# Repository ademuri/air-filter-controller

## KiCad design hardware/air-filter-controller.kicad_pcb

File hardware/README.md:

## Design decisions

### Power supply scheme

The ESP32-S3 uses 3.3V. I want onboard indicator LEDs, and the option to have offboard LEDs as well. Using addressable WS2812-type LEDs is flexible. These need a 5V supply. The fans draw 12V, so this necessitates two voltage regulators.

One option would be to use separate buck converters for both the 5V and 3.3V rails.

With no offboard LEDs, the 5V rail power draw will be low. WS2812B LEDs consume roughly 1mA each when idle. When lit at a fully-saturated color, they will consume about 20mA each. There are four onboard LEDs, so this means 4mA idle, and 80mA when lit.

This is relatively low power consumption. However, offboard LEDs may need significantly more power. If, for example, a 16-LED ring is used, then up to 400mA total may be needed.

During normal operation, the indicator light will be off. So, most of the time, the 5V current draw will be low.

To convert from the 12V supply to 5V, we'll use a buck converter. If we size the inductor for the maximum current draw, then the converter will potentially be noisy during typical operation.

So, we should instead use a linear regulator to convert the 5V to 3.3V, if possible. This will simplify the design, and increase the minimum current draw on the buck converter. Is it feasible?

The ESP32-S3 datasheet says that the power supply should support at least 500mA. The AMS1117-3.3 supports 1A max. The typical power draw of the ESP32-S3 running our ESPHome configuration is 30-120mA. A linear regulator burns the excess voltage as heat. For (worst-case) typical operation, the power consumed by the regulator will be `.12A * (5V - 3.3V) = 200mW`. This is acceptable.

Using [this buck converter calculator](http://schmidt-walter-schaltnetzteile.de/smps_e/abw_smps_e.html), a 100uH inductor means that the maximum ripple current will be about 50mA.

The chosen inductor (`SWPA8065S101MT`) has a max DC resistance of 0.28Ω, and a max heat-rating current of 1.35A. If the ESP32-S3 draws 500mA, this leaves >500mA for LEDs. This is sufficient.

#### Filtering

I did a conducted emissions pre-test for v1.0, using a dual 5uH LISN between the board and an adjustable DC power supply. With the board on and idle (30-40mA pulled from the 12V source), I saw a few concerning peaks:

- A sharp peak around 725 kHz, about 10dB above the limit
- Sharp peaks around 3.6kHz, 1.4 MHz, 2.2 MHz, and 3.6 MHz - these are >3dB below the limit
- Broadband noise between 300kHz to 400kHz

Increasing the load on the buck converter slightly by turning on the indicator LED to full white (50-55mA pulled @12V), the peaks get sharper, with the 365 kHz peak exceeding the limit by 6dB, and the 1.4MHz peak exceeding the limit by ~8dB.

There isn't much change with one fan plugged in on full power.

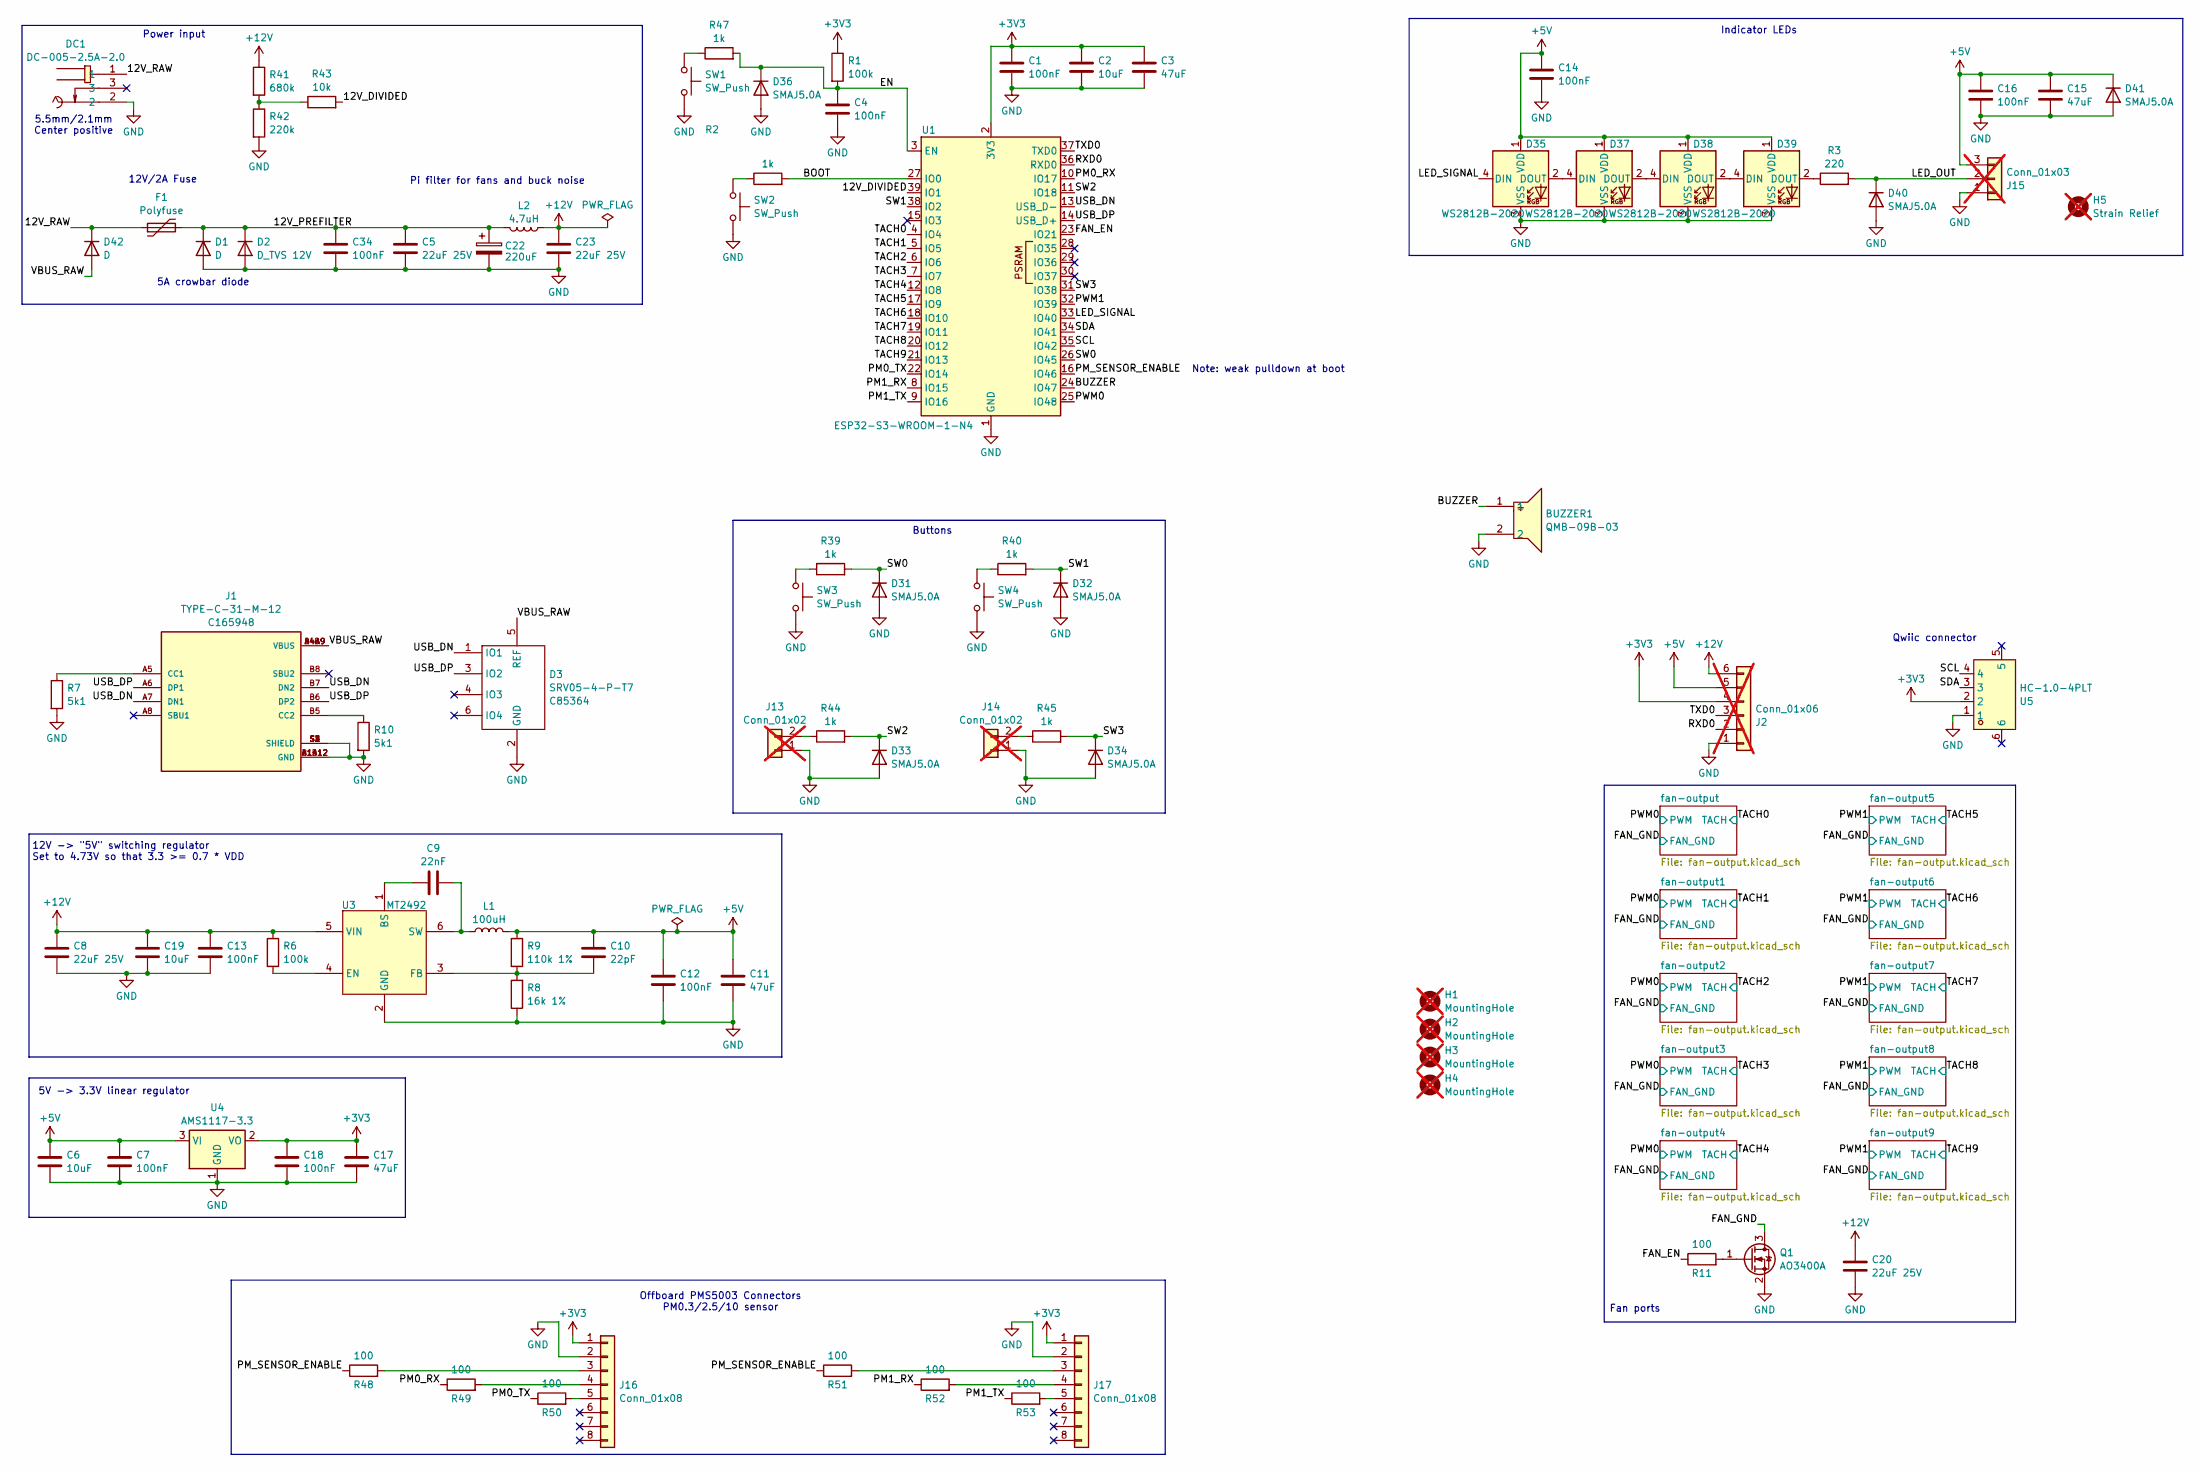
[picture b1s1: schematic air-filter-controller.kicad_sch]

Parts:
BUZZER1: QMB-09B-03; BUZ-TH_BD9.0-P4.00-D0.6-FD; LCSC C96256
C1, C4, C7, C12, C13, C14, C16, C18, C34: 100nF; C_0402_1005Metric; LCSC C307331
C2, C6, C19: 10uF; C_0603_1608Metric; LCSC C96446
C3, C11, C15, C17: 47uF; C_1206_3216Metric; LCSC C96123
C5, C8, C20, C23: 22uF 25V; C_1206_3216Metric; LCSC C12891
C9: 22nF; C_0402_1005Metric; LCSC C1532
C10: 22pF; C_0402_1005Metric; LCSC C1555
C22: 220uF; CP_Elec_8x10; LCSC C134765
D1, D42: D; D_SMA; MPN SS54; LCSC C22452
D2: D_TVS 12V; D_SMA; MPN SMAJ12A-E3/61; LCSC C89613
D3: SRV05-4-P-T7; SOT-23-6; LCSC C85364
D31, D32, D33, D34, D36, D40, D41: SMAJ5.0A; D_SMA; MPN SMAJ5.0A; LCSC C113952
D35, D37, D38, D39: WS2812B-2020; LED-SMD_4P-L2.0-W2.0-TL_WS2812B-2020; LCSC C965555
DC1: DC-005-2.5A-2.0; CONN-TH_DC-005-2.5A-2.0; LCSC C319099
F1: Polyfuse; Fuse_1812_4532Metric; MPN 1812L200/12DR; LCSC C315901
H1, H2, H3, H4: MountingHole; MountingHole_3.2mm_M3_ISO7380; not fitted
H5: Strain Relief; 3_pin_2.54mm_pitch_strain_relief; not fitted
J1: TYPE-C-31-M-12; HRO_TYPE-C-31-M-12; PARTREV A; LCSC C165948
J2: Conn_01x06; PinHeader_1x06_P2.54mm_Vertical; not fitted
J13, J14: Conn_01x02; PinHeader_1x02_P2.54mm_Vertical; not fitted
J15: Conn_01x03; PinHeader_1x03_P2.54mm_Vertical; not fitted
J16, J17: Conn_01x08; CONN-TH_8P-P1.25_HCTL_HC-1.25-8A; LCSC C2845526
L1: 100uH; L_Sunlord_SWPA8040S; MPN SWPA8065S101MT; LCSC C334254
L2: 4.7uH; L_Sunlord_SWPA4030S; MPN SWPA4030S4R7MT; LCSC C57269
Q1: AO3400A; SOT-23; LCSC C20917
R1, R6: 100k; R_0402_1005Metric; LCSC C25741
R2, R39, R40, R44, R45, R47: 1k; R_0402_1005Metric; LCSC C11702
R3: 220; R_0603_1608Metric_Pad0.98x0.95mm_HandSolder; LCSC C22962
R7, R10: 5k1; R_0402_1005Metric; LCSC C25905
R8: 16k 1%; R_0402_1005Metric; LCSC C25759
R9: 110k 1%; R_0402_1005Metric; LCSC C25745
R11: 100; R_0402_1005Metric; LCSC C25076
R41: 680k; R_0402_1005Metric; LCSC C4131
R42: 220k; R_0402_1005Metric; LCSC C25767
R43: 10k; R_0402_1005Metric; LCSC C25744
R48, R49, R50, R51, R52, R53: 100; R_0603_1608Metric_Pad0.98x0.95mm_HandSolder; LCSC C22775
SW1, SW2, SW3, SW4: SW_Push; SW_TACTILE_5.1MM_TS-1187A-C-D-B; LCSC C318884
U1: ESP32-S3-WROOM-1-N4; ESP32-S3-WROOM-1; LCSC C2913197
U3: MT2492; SOT-23-6_L2.9-W1.6-P0.95-LS2.8-BL; LCSC C89358
U4: AMS1117-3.3; SOT-223-3_TabPin2; LCSC C6186
U5: HC-1.0-4PLT; CONN-SMD_4P-P1.00_HC-1.0-4PLT; LCSC C2845372

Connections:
+3V3: C1.1, C2.1, C3.1, C17.1, C18.1, J2.4, J16.1, J17.1, R1.1, U1.2 (3V3), U4.2 (VO), U5.2; also elsewhere on the board
+5V: C6.1, C7.1, C10.2, C11.1, C12.1, C14.1, C15.1, C16.1, D35.1 (VDD), D37.1 (VDD), D38.1 (VDD), D39.1 (VDD), D41.1 (K), J2.5, J15.3, L1.2, R9.1, U4.3 (VI)
+12V: C8.1, C13.1, C19.1, C20.1, C23.1, J2.6, L2.1, R6.1, R41.1, U3.5 (VIN); also elsewhere on the board
/12V_DIVIDED: R43.2, U1.39 (IO1)
/12V_PREFILTER: C5.1, C22.1, C34.1, D1.1 (K), D2.1 (K), F1.2, L2.2
/12V_RAW: D42.1 (K), DC1.1, F1.1
/BOOT: R2.2, U1.27 (IO0)
/BUZZER: BUZZER1.1, U1.24 (IO47)
/EN: C4.1, D36.1 (K), R1.2, R47.2, U1.3 (EN)
/FAN_EN: R11.1, U1.23 (IO21)
/FAN_GND: Q1.3 (D); also elsewhere on the board
/LED_OUT: D40.1 (K), J15.2, R3.2
/LED_SIGNAL: D35.4 (DIN), U1.33 (IO40)
/PM0_RX: R49.1, U1.10 (IO17)
/PM0_TX: R50.1, U1.22 (IO14)
/PM1_RX: R52.1, U1.8 (IO15)
/PM1_TX: R53.1, U1.9 (IO16)
/PM_SENSOR_ENABLE: R48.1, R51.1, U1.16 (IO46)
/PWM0: U1.25 (IO48); also elsewhere on the board
/PWM1: U1.32 (IO39); also elsewhere on the board
/RXD0: J2.2, U1.36 (RXD0)
/SCL: U1.35 (IO42), U5.4
/SDA: U1.34 (IO41), U5.3
/SW0: D31.1 (K), R39.2, U1.26 (IO45)
/SW1: D32.1 (K), R40.2, U1.38 (IO2)
/SW2: D33.1 (K), R44.2, U1.11 (IO18)
/SW3: D34.1 (K), R45.2, U1.31 (IO38)
/TACH0: U1.4 (IO4); also elsewhere on the board
/TACH1: U1.5 (IO5); also elsewhere on the board
/TACH2: U1.6 (IO6); also elsewhere on the board
/TACH3: U1.7 (IO7); also elsewhere on the board
/TACH4: U1.12 (IO8); also elsewhere on the board
/TACH5: U1.17 (IO9); also elsewhere on the board
/TACH6: U1.18 (IO10); also elsewhere on the board
/TACH7: U1.19 (IO11); also elsewhere on the board
/TACH8: U1.20 (IO12); also elsewhere on the board
/TACH9: U1.21 (IO13); also elsewhere on the board
/TXD0: J2.3, U1.37 (TXD0)
/USB_DN: D3.1 (IO1), J1.A7 (DN1), J1.B7 (DN2), U1.13 (USB_D-)
/USB_DP: D3.3 (IO2), J1.A6 (DP1), J1.B6 (DP2), U1.14 (USB_D+)
/VBUS_RAW: D3.5 (REF), D42.2 (A), J1.A4B9 (VBUS), J1.B4A9 (VBUS)
GND: BUZZER1.2, C1.2, C2.2, C3.2, C4.2, C5.2, C6.2, C7.2, C8.2, C11.2, C12.2, C13.2, C14.2, C15.2, C16.2, C17.2, C18.2, C19.2, C20.2, C22.2, C23.2, C34.2, D1.2 (A), D2.2 (A), D3.2 (GND), D31.2 (A), D32.2 (A), D33.2 (A), D34.2 (A), D35.3 (VSS), D36.2 (A), D37.3 (VSS), D38.3 (VSS), D39.3 (VSS), D40.2 (A), D41.2 (A), DC1.2, J1.A1B12 (GND), J1.B1A12 (GND), J1.S1 (SHIELD), J1.S2 (SHIELD), J1.S3 (SHIELD), J1.S4 (SHIELD), J2.1, J13.1, J14.1, J15.1, J16.2, J17.2, Q1.2 (S), R7.2, R8.1, R10.2, R42.2, SW1.2, SW2.2, SW3.2, SW4.2, U1.1 (GND), U1.40 (GND), U1.41 (GND), U3.2 (GND), U4.1 (GND), U5.1; also elsewhere on the board
unnamed: D35.2 (DOUT), D37.4 (DIN)
unnamed: D37.2 (DOUT), D38.4 (DIN)
unnamed: D38.2 (DOUT), D39.4 (DIN)
unnamed: D39.2 (DOUT), R3.1
unnamed: J1.A5 (CC1), R7.1
unnamed: J1.B5 (CC2), R10.1
unnamed: J13.2, R44.1
unnamed: J14.2, R45.1
unnamed: J16.3, R48.2
unnamed: J16.4, R49.2
unnamed: J16.5, R50.2
unnamed: J17.3, R51.2
unnamed: J17.4, R52.2
unnamed: J17.5, R53.2
unnamed: Q1.1 (G), R11.2
unnamed: R2.1, SW2.1
unnamed: R39.1, SW3.1
unnamed: R40.1, SW4.1
unnamed: R41.2, R42.1, R43.1
unnamed: R47.1, SW1.1
unnamed: C9.1, U3.1 (BS)
unnamed: R6.2, U3.4 (EN)
unnamed: C10.1, R8.2, R9.2, U3.3 (FB)
unnamed: C9.2, L1.1, U3.6 (SW)

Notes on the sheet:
Power input
Fan ports
Note: weak pulldown at boot
Pi filter for fans and buck noise
5.5mm/2.1mm Center positive
5V -> 3.3V linear regulator
Qwiic connector
12V -> "5V" switching regulator Set to 4.73V so that 3.3 >= 0.7 * VDD
Offboard PMS5003 Connectors PM0.3/2.5/10 sensor
5A crowbar diode
12V/2A Fuse
Indicator LEDs
Buttons

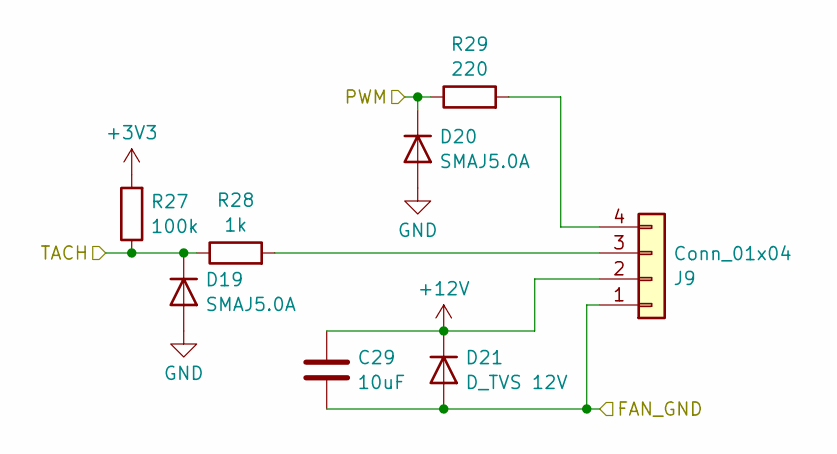
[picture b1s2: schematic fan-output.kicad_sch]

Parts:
C29: 10uF; C_0603_1608Metric; LCSC C96446
D19, D20: SMAJ5.0A; D_SMA; MPN SMAJ5.0A; LCSC C113952
D21: D_TVS 12V; D_SMA; MPN SMAJ12A-E3/61; LCSC C89613
J9: Conn_01x04; CONN-TH_47053-1000; MPN 470531000; LCSC C240840
R27: 100k; R_0603_1608Metric_Pad0.98x0.95mm_HandSolder; LCSC C25803
R28: 1k; R_0402_1005Metric; LCSC C11702
R29: 220; R_0603_1608Metric_Pad0.98x0.95mm_HandSolder; LCSC C22962

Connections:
+3V3: R27.2; also elsewhere on the board
+12V: C29.1, D21.1 (K), J9.2; also elsewhere on the board
/FAN_GND: C29.2, D21.2 (A), J9.1; also elsewhere on the board
/PWM1: D20.1 (K), R29.1; also elsewhere on the board
/TACH5: D19.1 (K), R27.1, R28.1; also elsewhere on the board
GND: D19.2 (A), D20.2 (A); also elsewhere on the board
unnamed: J9.3, R28.2
unnamed: J9.4, R29.2

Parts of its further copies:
C24, C25, C26, C27, C28, C30, C31, C32, C33: 10uF; C_0603_1608Metric; LCSC C96446
D4, D9, D12, D15, D18, D24, D27, D30, D45: D_TVS 12V; D_SMA; MPN SMAJ12A-E3/61; LCSC C89613
D5, D6, D7, D8, D10, D11, D13, D14, D16, D17, D22, D23, D25, D26, D28, D29, D43, D44: SMAJ5.0A; D_SMA; MPN SMAJ5.0A; LCSC C113952
J3, J4, J5, J6, J7, J8, J10, J11, J12: Conn_01x04; CONN-TH_47053-1000; MPN 470531000; LCSC C240840
R4, R12, R15, R18, R21, R24, R30, R33, R36: 100k; R_0603_1608Metric_Pad0.98x0.95mm_HandSolder; LCSC C25803
R5, R13, R16, R19, R22, R25, R31, R34, R37: 1k; R_0402_1005Metric; LCSC C11702
R14, R17, R20, R23, R26, R32, R35, R38, R46: 220; R_0603_1608Metric_Pad0.98x0.95mm_HandSolder; LCSC C22962

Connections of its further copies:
+3V3: R4.2, R12.2, R15.2, R18.2, R21.2, R24.2, R30.2, R33.2, R36.2; also elsewhere on the board
+12V: C24.1, C25.1, C26.1, C27.1, C28.1, C30.1, C31.1, C32.1, C33.1, D4.1 (K), D9.1 (K), D12.1 (K), D15.1 (K), D18.1 (K), D24.1 (K), D27.1 (K), D30.1 (K), D45.1 (K), J3.2, J4.2, J5.2, J6.2, J7.2, J8.2, J10.2, J11.2, J12.2; also elsewhere on the board
/FAN_GND: C24.2, C25.2, C26.2, C27.2, C28.2, C30.2, C31.2, C32.2, C33.2, D4.2 (A), D9.2 (A), D12.2 (A), D15.2 (A), D18.2 (A), D24.2 (A), D27.2 (A), D30.2 (A), D45.2 (A), J3.1, J4.1, J5.1, J6.1, J7.1, J8.1, J10.1, J11.1, J12.1; also elsewhere on the board
/PWM0: D6.1 (K), D8.1 (K), D11.1 (K), D14.1 (K), D17.1 (K), R14.1, R17.1, R20.1, R23.1, R26.1; also elsewhere on the board
/PWM1: D23.1 (K), D26.1 (K), D29.1 (K), D44.1 (K), R32.1, R35.1, R38.1, R46.1; also elsewhere on the board
/TACH0: D5.1 (K), R13.1, R15.1; also elsewhere on the board
/TACH1: D7.1 (K), R12.1, R16.1; also elsewhere on the board
/TACH2: D10.1 (K), R18.1, R19.1; also elsewhere on the board
/TACH3: D13.1 (K), R21.1, R22.1; also elsewhere on the board
/TACH4: D16.1 (K), R24.1, R25.1; also elsewhere on the board
/TACH6: D22.1 (K), R30.1, R31.1; also elsewhere on the board
/TACH7: D25.1 (K), R33.1, R34.1; also elsewhere on the board
/TACH8: D28.1 (K), R36.1, R37.1; also elsewhere on the board
/TACH9: D43.1 (K), R4.1, R5.1; also elsewhere on the board
GND: D5.2 (A), D6.2 (A), D7.2 (A), D8.2 (A), D10.2 (A), D11.2 (A), D13.2 (A), D14.2 (A), D16.2 (A), D17.2 (A), D22.2 (A), D23.2 (A), D25.2 (A), D26.2 (A), D28.2 (A), D29.2 (A), D43.2 (A), D44.2 (A); also elsewhere on the board
unnamed: J3.3, R16.2
unnamed: J3.4, R17.2
unnamed: J4.3, R5.2
unnamed: J4.4, R46.2
unnamed: J5.3, R13.2
unnamed: J5.4, R14.2
unnamed: J6.3, R19.2
unnamed: J6.4, R20.2
unnamed: J7.3, R22.2
unnamed: J7.4, R23.2
unnamed: J8.3, R25.2
unnamed: J8.4, R26.2
unnamed: J10.3, R31.2
unnamed: J10.4, R32.2
unnamed: J11.3, R34.2
unnamed: J11.4, R35.2
unnamed: J12.3, R37.2
unnamed: J12.4, R38.2

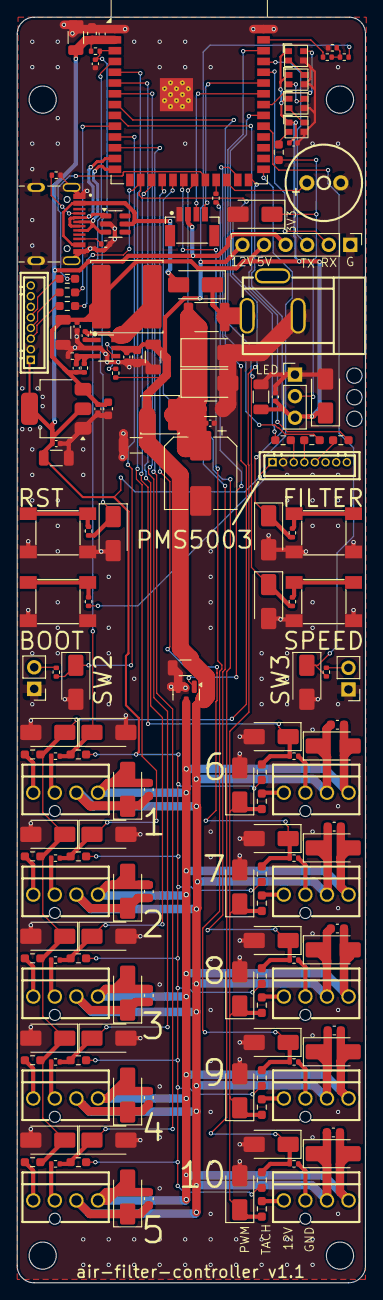
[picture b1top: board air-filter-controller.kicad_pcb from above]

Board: 4 copper layers, 41.0 x 149.0 mm, 167 parts (0 on the bottom side), 86 nets.

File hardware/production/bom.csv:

Designator,Footprint,Quantity,Value,LCSC Part #
BUZZER1,BUZ-TH_BD9.0-P4.00-D0.6-FD,1,QMB-09B-03,
"C1, C12, C13, C14, C16, C18, C34, C4, C7",0402,9,100nF,C307331
C10,0402,1,22pF,C1555
"C11, C15, C17, C3",1206,4,47uF,C96123
"C19, C2, C24, C25, C26, C27, C28, C29, C30, C31, C32, C33, C6",0603,13,10uF,C96446
"C20, C23, C5, C8",1206,4,22uF 25V,C12891
C22,CP_Elec_8x10,1,220uF,C134765
C9,0402,1,22nF,C1532
"D1, D42",D_SMA,2,D,C22452
"D10, D11, D13, D14, D16, D17, D19, D20, D22, D23, D25, D26, D28, D29, D31, D32, D33, D34, D36, D40, D41, D43, D44, D5, D6, D7, D8",D_SMA,27,SMAJ5.0A,C113952
"D12, D15, D18, D2, D21, D24, D27, D30, D4, D45, D9",D_SMA,11,D_TVS 12V,C89613
D3,SOT-23-6,1,SRV05-4-P-T7,C85364
"D35, D37, D38, D39",LED-SMD_4P-L2.0-W2.0-TL_WS2812B-2020,4,WS2812B-2020,C965555
DC1,CONN-TH_DC-005-2.5A-2.0,1,DC-005-2.5A-2.0,C319099
F1,1812,1,Polyfuse,C315901
J1,HRO_TYPE-C-31-M-12,1,TYPE-C-31-M-12,C165948
"J10, J11, J12, J3, J4, J5, J6, J7, J8, J9",CONN-TH_47053-1000,10,Conn_01x04,C240840
"J16, J17",CONN-TH_8P-P1.25_HCTL_HC-1.25-8A,2,Conn_01x08,C2845526
L1,L_Sunlord_SWPA8040S,1,100uH,C334254
L2,L_Sunlord_SWPA4030S,1,4.7uH,C57269
Q1,SOT-23,1,AO3400A,C20917
"R1, R6",0402,2,100k,C25741
"R10, R7",0402,2,5k1,C25905
R11,0402,1,100,C25076
"R12, R15, R18, R21, R24, R27, R30, R33, R36, R4",0603,10,100k,C25803
"R13, R16, R19, R2, R22, R25, R28, R31, R34, R37, R39, R40, R44, R45, R47, R5",0402,16,1k,C11702
"R14, R17, R20, R23, R26, R29, R3, R32, R35, R38, R46",0603,11,220,C22962
R41,0402,1,680k,C4131
R42,0402,1,220k,C25767
R43,0402,1,10k,C25744
"R48, R49, R50, R51, R52, R53",0603,6,100,C22775
R8,0402,1,16k 1%,C25759
R9,0402,1,110k 1%,C25745
"SW1, SW2, SW3, SW4",SW_TACTILE_5.1MM_TS-1187A-C-D-B,4,SW_Push,C318884
U1,ESP32-S3-WROOM-1,1,ESP32-S3-WROOM-1-N4,C2913197
U3,SOT-23-6_L2.9-W1.6-P0.95-LS2.8-BL,1,MT2492,
U4,SOT-223-3_TabPin2,1,AMS1117-3.3,C6186
U5,CONN-SMD_4P-P1.00_HC-1.0-4PLT,1,HC-1.0-4PLT,C2845372

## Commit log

2024-06-15 Start adding schematic
2024-06-15 Add gitignores
2024-06-15 First pass at schematic
2024-06-15 Add buzzer
2024-06-18 Start placement and routing
2024-06-30 Routing and placement done
2024-06-30 Hardware v1.0
2024-06-30 Add basic ESPHome template.
    This sets up the platform config, and includes the buzzer.
2024-07-03 WIP configure some of ESPHome
2024-07-07 Configure buzzer and one tach
2024-07-13 WIP debug BMP280
2024-07-18 Configure BMP280 (forked repo) and buttons
2024-07-18 Simplify fan power control
2024-07-18 Add filter runtime monitoring
2024-07-18 Rename template
2024-07-19 Add script for measuring filter pressure drop
2024-07-19 Set units for pressure drop
2024-07-21 Add scripts for logging pressure changes
2024-07-22 Improve filter test routine
2024-08-07 Export max tach sensor
2024-08-07 Increase update interval for time since filter check
2024-08-09 Toggle speeds when speed button is pressed
2024-10-19 Add example usage of template
2024-10-20 Remove BMP280 from config
2024-10-20 Add remaining tachos
2024-10-25 Add min tach logic
2024-10-25 Add local min tach functionality
2024-10-25 Add CI config to build example.yaml
2024-10-25 Remove underscore in example name to fix CI warning
2024-10-31 More schematic updates for v1.1
2024-11-02 Clear ERC exclusions
2024-11-03 Add ADP2100 differential pressure sensor
2024-11-03 Clean up ADP2100
2024-11-03 Forget .pyc file
2024-11-03 Add temperature and CRC checking to ADP2100
2024-11-06 Only collect filter drop when fan is at full speed
2024-11-06 Forget pyc file
2024-12-24 Update device class; show no value when fan speed not at full
2024-12-28 More schematic updates for v1.1:
    - Add connectors for offboard PMS5003 sensors
    - Add ADP2100 differential pressure sensor
2024-12-29 v1.1: start updating layout
2024-12-30 Hardware revision v1.1:
    - Fix flipped USB lines
    - Remove diode on BOOT switch
    - Remove buzzer resistor
    - Change voltage divider to ADC channel 1
    - Increased from 9 to 10 fan channels
    - Switched to addressable LEDs
2025-01-06 WIP address conducted emissions
2025-01-10 Update pre-compliance test info in readme
2025-01-30 Hardware v1.1
2025-01-30 Add PMS5003
2025-03-27 Update template metadata
2025-03-27 Add filter runtime reset functionality
2025-03-27 Update CI dependencies
2025-06-20 Add sensor for template version
2025-06-20 Update CI build version
